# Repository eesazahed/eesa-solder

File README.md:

# eesa-solder

I made this to be an Attack on Titan keychain with LEDs. I followed [solder.hackclub.com/tutorial](https://solder.hackclub.com/tutorial) and used the following parts:

- LED
- R
- SW_SPST
- Battery_Cell

<br /><br />

<br /><br />

<br /><br />

<br /><br />
<br /><br />

My Slack username: [@Eesa](https://hackclub.slack.com/team/U074SFQFJMS)

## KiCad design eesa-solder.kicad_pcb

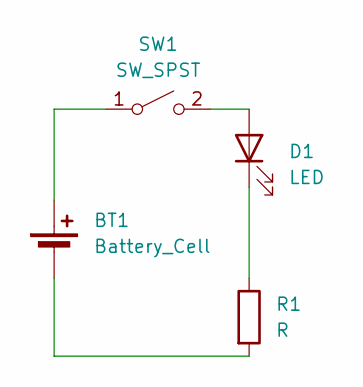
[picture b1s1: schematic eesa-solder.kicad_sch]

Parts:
BT1: Battery_Cell; BatteryHolder_Keystone_3034_1x20mm
D1: LED; LED_D5.0mm
R1: R; R_Axial_DIN0207_L6.3mm_D2.5mm_P7.62mm_Horizontal
SW1: SW_SPST; SW_Slide_SPDT_Straight_CK_OS102011MS2Q

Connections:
unnamed: BT1.1 (+), SW1.1 (A)
unnamed: BT1.2 (-), R1.2
unnamed: D1.2 (A), SW1.2 (B)
unnamed: D1.1 (K), R1.1

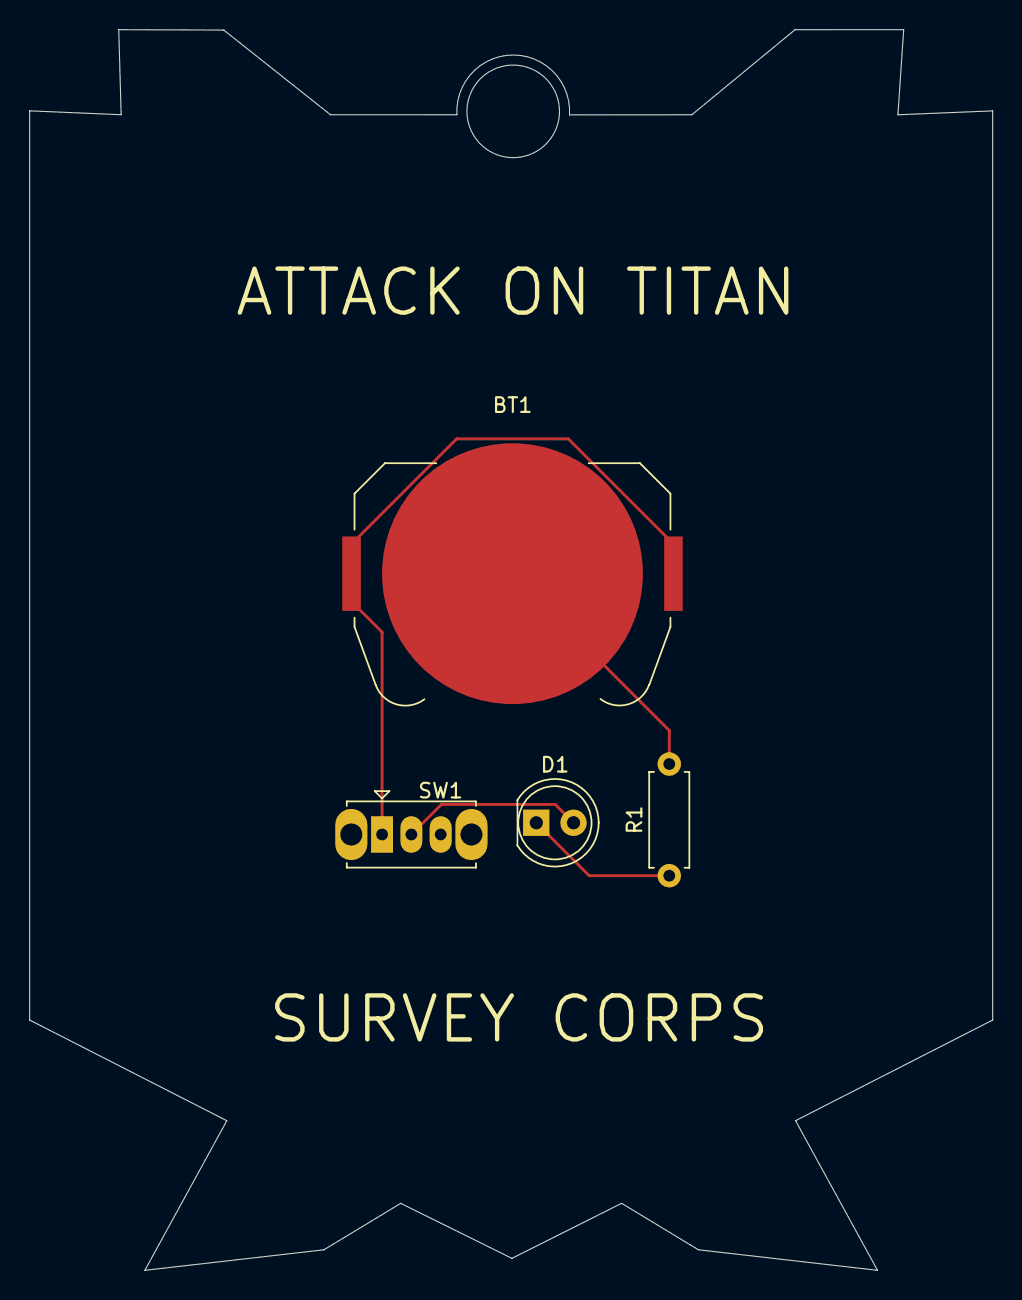
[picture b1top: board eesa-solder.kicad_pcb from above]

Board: 2 copper layers, 65.7 x 84.7 mm, 4 parts (0 on the bottom side), 4 nets.

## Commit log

2025-07-28 prod
2025-07-28 push to github
2025-07-28 edit parts
2025-07-28 plot
